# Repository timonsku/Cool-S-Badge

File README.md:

# Cool-S-Badge

Targets nRF Connect 3.1.1

For Assembly check the docs folder.
TRIPPLE CHECK THE PRO MICRO ORIENTATION before soldering in place

Always update the firmware with the latest version committed to the root of the repo.

OTA Firmware Update
----------------
Download Nordic Device Manager and select the zip file in the DFU/Image tab.
Takes about 30sec after upload before it comes back online.
https://www.nordicsemi.com/Products/Development-tools/nRF-Connect-Device-Manager

Step by step instructions can be found in [OTA.md](docs/OTA/OTA.md)

How to set colors
----------------
Use the "iPixel Color" app in "DIY Drawing" mode to apply LED colors.
Animation support coming soon, bit buggy right now.
Brightness adjustment in Settings menu works but does not persists right now.
Colors persist through reboots if you pressed OK in the editor.

Click the big plus sign to find devices. They are called "LED_XXXXXXXX". With XXXXXXXX being the last four bytes of the MAC address.

Android: https://play.google.com/store/apps/details?id=com.wifiled.ipixels&hl=en

iOS: https://apps.apple.com/us/app/ipixel-color/id1562961996

Turn On/Off
----------------
Press the bottom two buttons for 2 seconds and release to turn off. Press them again to turn back on.

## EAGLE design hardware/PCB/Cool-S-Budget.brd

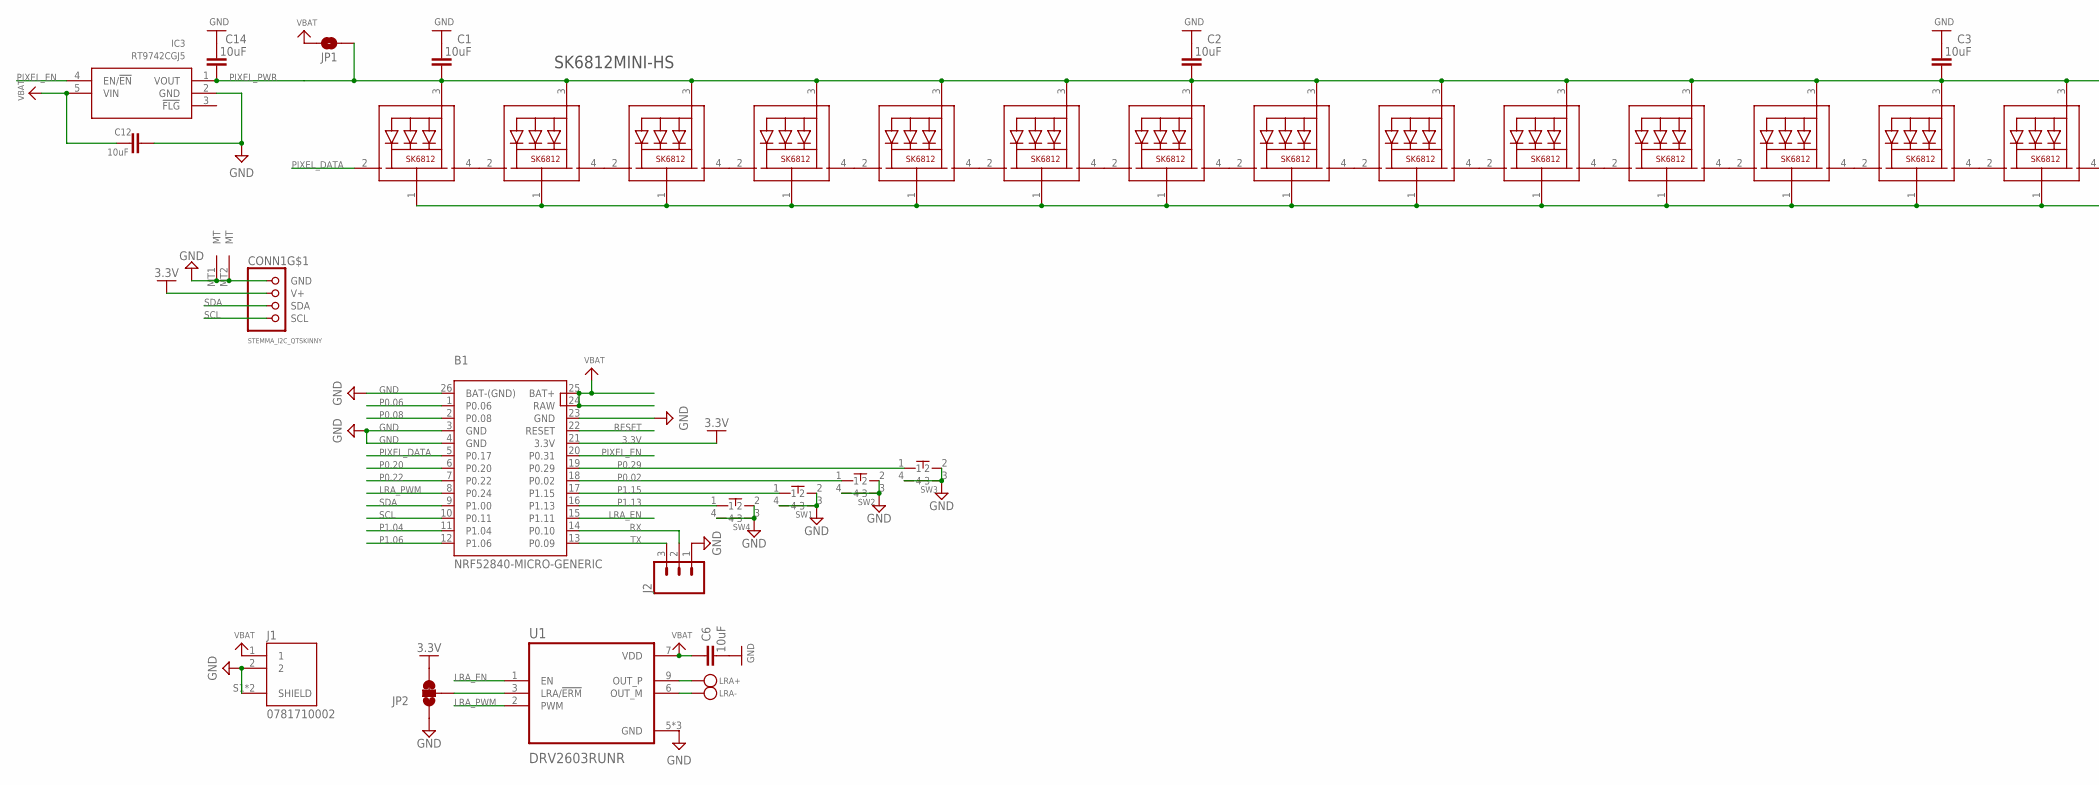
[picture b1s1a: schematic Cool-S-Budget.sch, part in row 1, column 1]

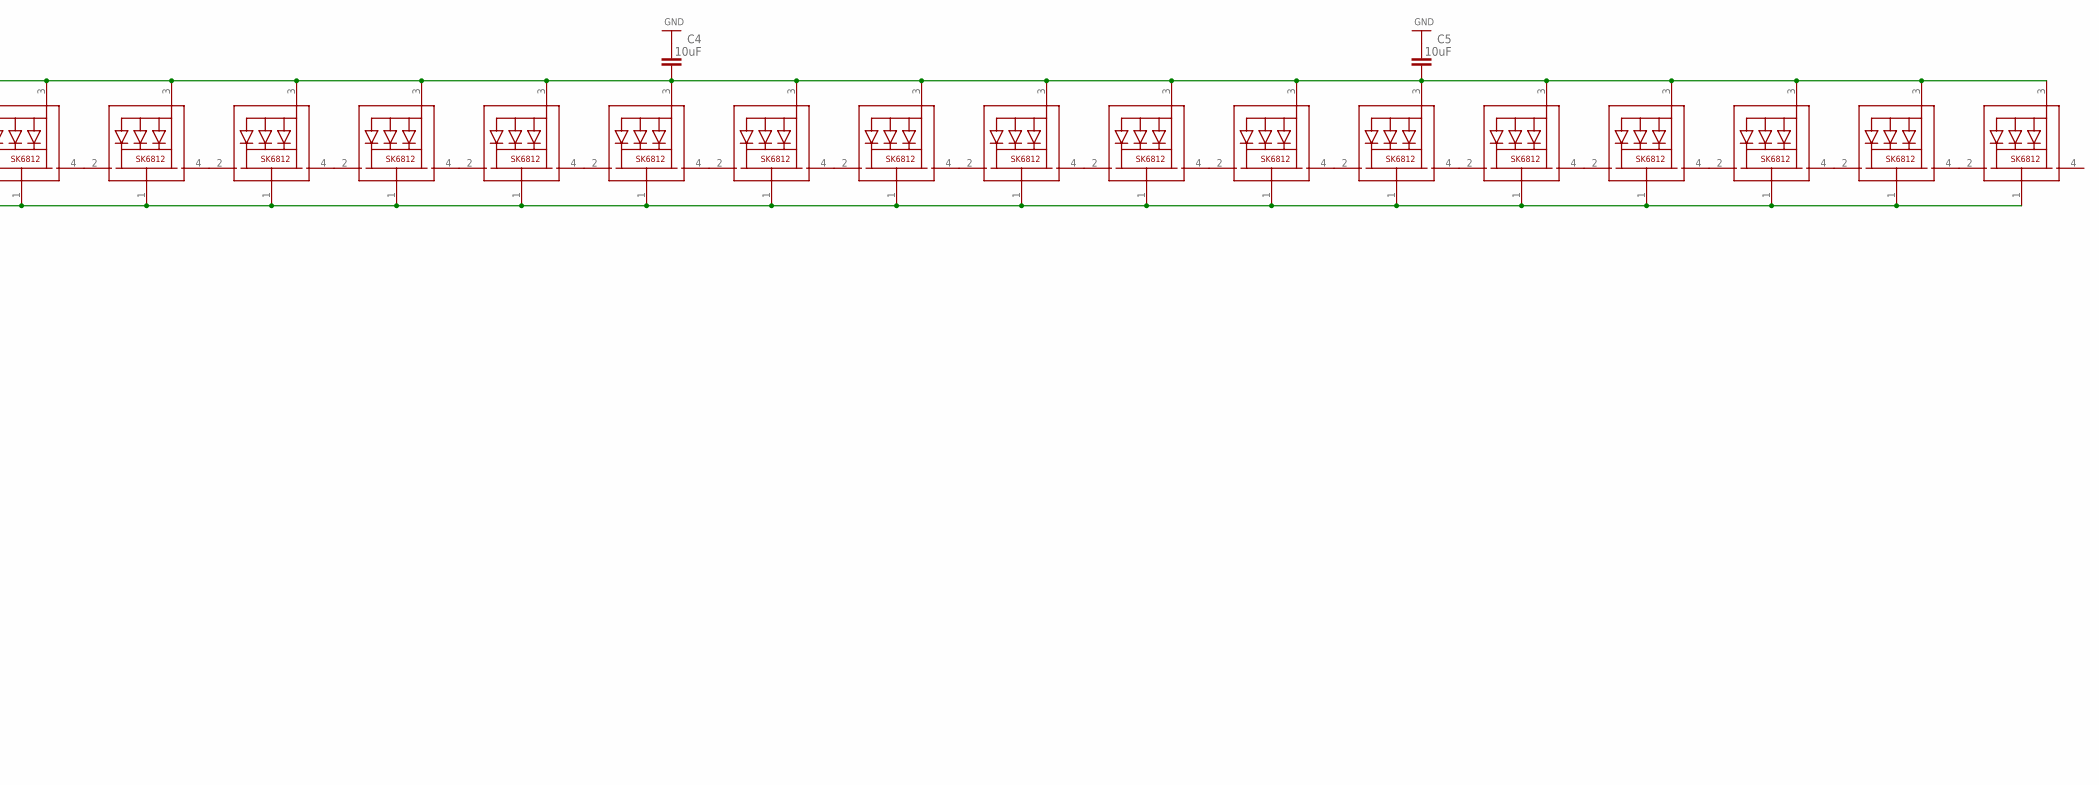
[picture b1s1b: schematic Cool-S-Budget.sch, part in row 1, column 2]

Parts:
B1: NRF52840-MICRO-GENERIC
C1, C2, C3, C4, C5, C6, C12, C14: 10uF; CAPC1608X85
CONN1: STEMMA_I2C_QTSKINNY; JST_SH4_SKINNY
IC3: RT9742CGJ5; SOT94P280X100-5N
J1: 0781710002; MOLEX_0781710002
J2: 455-1750-1-ND; 1X03
JP1: JUMPER-SMT_2_NO_NO-SILK; SMT-JUMPER_2_NO_NO-SILK
JP2: JUMPER-SMT_3_1-NC_TRACE_NO-SILK; SMT-JUMPER_3_1-NC_TRACE_NO-SILK
LRA+: TESTPOINT; TESTPOINT_SMT
LRA-: TESTPOINT; TESTPOINT_SMT
SW1, SW2, SW3, SW4: TS36CA-0.6250GF031SW-SMD_SHOU_TS36CA-0.6; SW-SMD_SHOU_TS36CA-0.6; LCSC C2906288
U1: DRV2603RUNR; QFN50P200X200X80-10N
U3, U4, U5, U6, U7, U8, U9, U10, U11, U12, U13, U14, U15, U16, U17, U18, U19, U20, U21, U22, U23, U24, U25, U26, U27, U28, U29, U30, U31, U32: SK6812MINI; LED3535

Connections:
3.3V: B1.21 (3.3V), CONN1.2 (V+), JP2.3
GND: B1.3 (GND), B1.4 (GND), B1.23 (GND), B1.26 (BAT-(GND)), C1.1, C2.1, C3.1, C4.1, C5.1, C6.1, C12.2, C14.1, CONN1.1 (GND), CONN1.MT1 (MT), CONN1.MT2 (MT), IC3.2 (GND), J1.2, J1.S1 (SHIELD), J1.S2 (SHIELD), J2.1, JP2.1, SW1.2, SW1.3, SW1.4, SW2.2, SW2.3, SW2.4, SW3.2, SW3.3, SW3.4, SW4.2, SW4.3, SW4.4, U1.5 (GND), U1.8 (GND), U1.10 (GND), U3.1 (GND), U4.1 (GND), U5.1 (GND), U6.1 (GND), U7.1 (GND), U8.1 (GND), U9.1 (GND), U10.1 (GND), U11.1 (GND), U12.1 (GND), U13.1 (GND), U14.1 (GND), U15.1 (GND), U16.1 (GND), U17.1 (GND), U18.1 (GND), U19.1 (GND), U20.1 (GND), U21.1 (GND), U22.1 (GND), U23.1 (GND), U24.1 (GND), U25.1 (GND), U26.1 (GND), U27.1 (GND), U28.1 (GND), U29.1 (GND), U30.1 (GND), U31.1 (GND), U32.1 (GND)
LRA+: LRA+.P$1, U1.9 (OUT_P)
LRA-: LRA-.P$1, U1.6 (OUT_M)
LRA_EN: B1.15 (P1.11), U1.1 (EN)
LRA_PWM: B1.8 (P0.24), U1.2 (PWM)
unnamed: U3.2 (DI), U4.4 (DO)
unnamed: U4.2 (DI), U5.4 (DO)
unnamed: U5.2 (DI), U6.4 (DO)
unnamed: U6.2 (DI), U7.4 (DO)
unnamed: U8.2 (DI), U9.4 (DO)
unnamed: U9.2 (DI), U10.4 (DO)
unnamed: U11.2 (DI), U12.4 (DO)
unnamed: U7.2 (DI), U8.4 (DO)
unnamed: U12.2 (DI), U13.4 (DO)
unnamed: U13.2 (DI), U14.4 (DO)
unnamed: U14.2 (DI), U15.4 (DO)
unnamed: U16.2 (DI), U17.4 (DO)
unnamed: U17.2 (DI), U18.4 (DO)
unnamed: U15.2 (DI), U16.4 (DO)
unnamed: U10.2 (DI), U11.4 (DO)
unnamed: U19.2 (DI), U20.4 (DO)
unnamed: U20.2 (DI), U21.4 (DO)
unnamed: U21.2 (DI), U22.4 (DO)
unnamed: U22.2 (DI), U23.4 (DO)
unnamed: U24.2 (DI), U25.4 (DO)
unnamed: U25.2 (DI), U26.4 (DO)
unnamed: U23.2 (DI), U24.4 (DO)
unnamed: U27.2 (DI), U28.4 (DO)
unnamed: U28.2 (DI), U29.4 (DO)
unnamed: U29.2 (DI), U30.4 (DO)
unnamed: U30.2 (DI), U31.4 (DO)
unnamed: JP2.2, U1.3 (LRA/!ERM)
unnamed: U31.2 (DI), U32.4 (DO)
unnamed: U26.2 (DI), U27.4 (DO)
unnamed: U18.2 (DI), U19.4 (DO)
P0.02: B1.18 (P0.02), SW2.1
P0.06: B1.1 (P0.06)
P0.08: B1.2 (P0.08)
P0.20: B1.6 (P0.20)
P0.22: B1.7 (P0.22)
P0.29: B1.19 (P0.29), SW3.1
P1.04: B1.11 (P1.04)
P1.06: B1.12 (P1.06)
P1.13: B1.16 (P1.13), SW4.1
P1.15: B1.17 (P1.15), SW1.1
PIXEL_DATA: B1.5 (P0.17), U32.2 (DI)
PIXEL_EN: B1.20 (P0.31), IC3.4 (EN/!EN)
PIXEL_PWR: C1.2, C2.2, C3.2, C4.2, C5.2, C14.2, IC3.1 (VOUT), JP1.1, U3.3 (VDD), U4.3 (VDD), U5.3 (VDD), U6.3 (VDD), U7.3 (VDD), U8.3 (VDD), U9.3 (VDD), U10.3 (VDD), U11.3 (VDD), U12.3 (VDD), U13.3 (VDD), U14.3 (VDD), U15.3 (VDD), U16.3 (VDD), U17.3 (VDD), U18.3 (VDD), U19.3 (VDD), U20.3 (VDD), U21.3 (VDD), U22.3 (VDD), U23.3 (VDD), U24.3 (VDD), U25.3 (VDD), U26.3 (VDD), U27.3 (VDD), U28.3 (VDD), U29.3 (VDD), U30.3 (VDD), U31.3 (VDD), U32.3 (VDD)
RESET: B1.22 (RESET)
RX: B1.14 (P0.10), J2.2
SCL: B1.10 (P0.11), CONN1.4 (SCL)
SDA: B1.9 (P1.00), CONN1.3 (SDA)
TX: B1.13 (P0.09), J2.3
VBAT: B1.24 (RAW), B1.25 (BAT+), C6.2, C12.1, IC3.5 (VIN), J1.1, JP1.2, U1.7 (VDD)

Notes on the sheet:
SK6812MINI-HS

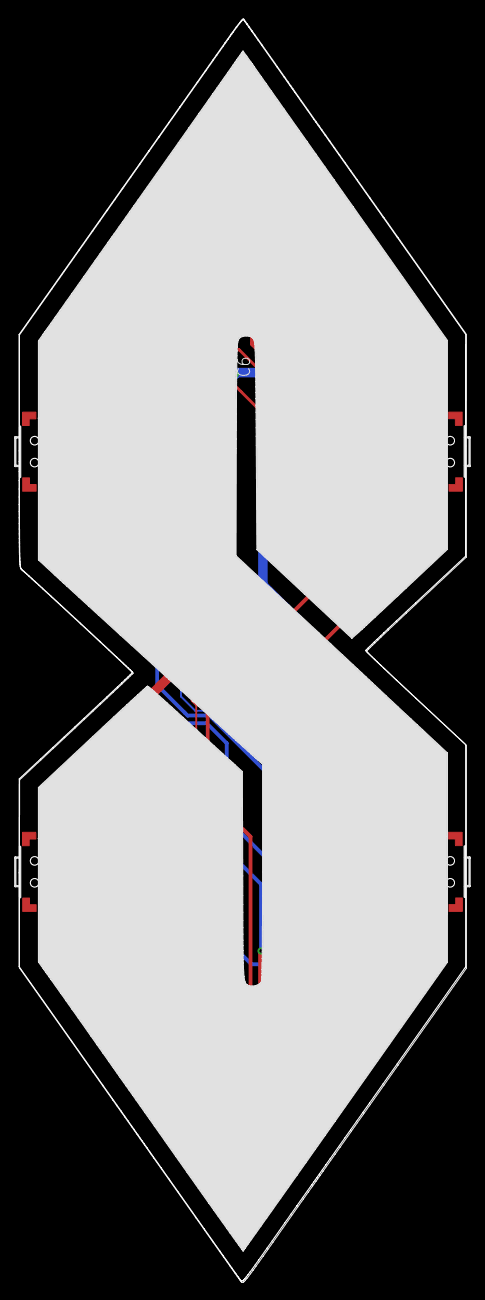
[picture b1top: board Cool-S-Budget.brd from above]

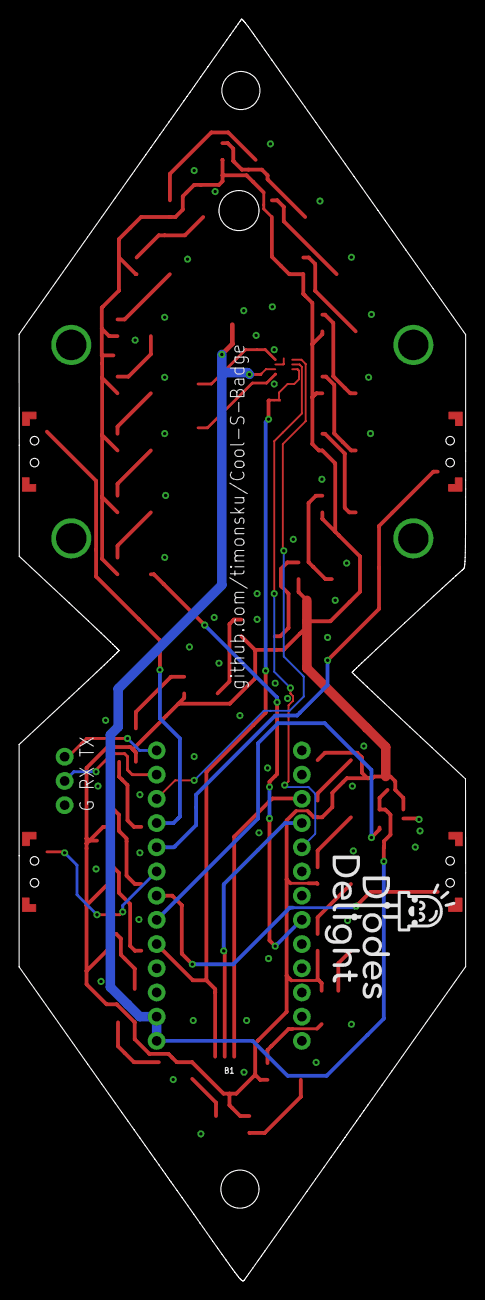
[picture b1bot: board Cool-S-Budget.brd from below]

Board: 2 copper layers, 46.9 x 132.4 mm, 53 parts (2 on the bottom side), 48 nets.

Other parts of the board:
U$4: DIODES-DELIGHT-LOGO-15X15

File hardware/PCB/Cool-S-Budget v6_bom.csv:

Comment,Designator,Footprint,LCSC Part #
10uF,C1 C2 C3 C4 C5 C6 C12 C14,603,C96446
781710002,J1,MOLEX_0781710002,
DRV2603RUNR,U1,QFN50P200X200X80-10N,
RT9742CGJ5,IC3,SOT94P280X100-5N,
STEMMA_I2C_QTSKINNY,CONN1,JST_SH4_SKINNY,C2845363
TS36CA-0.6250GF031SW-SMD_SHOU_TS36CA-0.6,SW1 SW2 SW3 SW4,SW-SMD_SHOU_TS36CA-0.6,C2906288
SK6812MINI-HS,U3 U4 U5 U6 U7 U8 U9 U10 U11 U12 U13 U14 U15 U16 U17 U18 U19 U20 U21 U22 U23 U24 U25 U26 U27 U28 U29 U30 U31 U32,SK6812MINI-HS,C2922787

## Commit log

2025-12-26 add initial release
2025-12-27 add minimal docs
2025-12-27 move docs folder
2025-12-27 add power instructions
2026-01-01 fix iPhone discovery for iPixel app
2026-01-01 OTA instructions
2026-01-01 update notices
2026-01-01 fix iOS pixel drawing

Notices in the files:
parts and their libraries:
microbuilder: This work is placed in the public domain, and may be freely used for commercial and non-commercial work with the following conditions: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
SparkFun-Jumpers: Licensing: Creative Commons ShareAlike 4.0 International - https://creativecommons.org/licenses/by-sa/4.0
